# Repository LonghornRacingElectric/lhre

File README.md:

# LHRe

Documentation: https://docs.lhre.org

Longhorn Racing Electric's monorepo: firmware for every ECU on the car, the
hardware abstraction layer it's built on, and the tooling to build, test, and
flash it all with Bazel.

<div class="grid cards" markdown>

-   :material-swap-horizontal:{ .lg .middle } **CAN Matrix & Signals**

    ---

    Full CAN ID allocation, message timings, signal bit layouts, and telemetry bindings generated from spec.

    [:octicons-arrow-right-24: Open CAN Matrix](docs/can-matrix.md){ .md-button .md-button--primary }

-   :material-chip:{ .lg .middle } **Boards & Firmware**

    ---

    Per-ECU firmware layout, the VCU reference board, pinouts, and the new-board scaffolder.

    [:octicons-arrow-right-24: Explore Boards](boards/README.md){ .md-button }

-   :material-layers-outline:{ .lg .middle } **LHAL & Drivers**

    ---

    Platform-independent hardware abstraction layer enabling 100% host-testable embedded code.

    [:octicons-arrow-right-24: Read LHAL Guide](drivers/lhal/README.md){ .md-button }

-   :material-bug-outline:{ .lg .middle } **Hardware Debugging**

    ---

    Zero-setup VS Code debugging with ST-Link, hermetic gdb, OpenOCD, and SVD peripheral viewer.

    [:octicons-arrow-right-24: Debugging Guide](tools/debug/README.md){ .md-button }

</div>

## Layout

| Directory  | What lives there |
| ---------- | ---------------- |
| [`drivers/`](drivers/README.md) | Hardware. [LHAL](drivers/lhal/README.md) (our platform-independent HAL) and [vendor HAL packages](drivers/stm32/README.md). |
| [`lib/`](lib/README.md)     | Platform-agnostic C++ that builds on host **and** target (ring buffers, CRC, CAN pack/unpack, …), with colocated tests. |
| [`apps/`](apps/README.md)    | Host-side software: telemetry, dashboards, gateways. |
| [`boards/`](boards/README.md)  | Per-ECU firmware projects ([`boards/VCU`](boards/VCU/README.md) is the reference layout). |
| [`tools/`](tools/README.md)   | Build and dev tooling: [`firmware_project`](tools/firmware/README.md), flashing, [VS Code debugging](tools/debug/README.md), formatting. |
| [`autonomy/`](https://github.com/LonghornRacingElectric/lhre/tree/main/autonomy) | The driverless stack: ROS 2 Jazzy + Gazebo, built with colcon rather than Bazel ([ADR-009](docs/architecture/009-autonomy-outside-bazel.md)). |
| [`simulation/`](simulation/README.md) | Vehicle dynamics studies on [BobSim](https://github.com/BobDyn/BobSim), run with Make and Docker rather than Bazel ([ADR-012](docs/architecture/012-simulation-outside-bazel.md)). |
| [`vehicle/`](vehicle/README.md) | The current car's parameters (`vehicle.yml`, tire models). One source for simulation and any Bazel target. |

There are no per-year directories: `main` is always the current car, and past
seasons live in tags and maintenance branches (see
[CONTRIBUTING.md](CONTRIBUTING.md#season-policy)).

The decisions that shape the repo — monorepo, Bazel, LHAL, docs conventions
— are recorded as ADRs in [docs/architecture](docs/architecture/README.md).
The build system gets its own long-form record — why Bazel, and the whys
behind its forks, pins, and patches — in
[docs/build-system.md](docs/build-system.md).

## Prerequisites

- [Bazelisk](https://github.com/bazelbuild/bazelisk) (installs the pinned
  Bazel from `.bazelversion` automatically)
- Git

That's it — compilers (ARM GCC for firmware, LLVM for host code) are hermetic
and downloaded by Bazel. No Xcode, MSVC, or system GCC needed for C++, and
no MSYS2 or Git Bash on Windows: builds there are shell-free
([ADR-018](docs/architecture/018-windows-shell-free.md)).
STM32CubeMX is only needed when changing a board's peripheral configuration.

On Windows, builds run locally instead of on remote executors; for full remote
execution use WSL2 (see the comments in [.bazelrc](https://github.com/LonghornRacingElectric/lhre/blob/main/.bazelrc)).
Windows also needs the `startup --output_user_root=C:/_bzl` line uncommented
in `.bazelrc.user` (copied from
[.bazelrc.user.example](https://github.com/LonghornRacingElectric/lhre/blob/main/.bazelrc.user.example)) —
without it, Python codegen tools blow Windows' 260-char path limit and die
with an `ImportError` in the protobuf runtime.

## The commands

Everything goes through Bazel, and the surface is small enough to memorize.
Shown for the VCU; swap `VCU`/`vcu` for any board — the targets are uniform
because [`firmware_project`](tools/firmware/README.md) generates them.

| To…                        | Run |
| -------------------------- | --- |
| Build one board's firmware | `bazel build //boards/VCU:vcu` |
| Build + test everything    | `bazel test //...` |
| Test host C++ under UBSan  | `bazel test --config=ubsan //boards/... //drivers/...` ([more](tools/ubsan/README.md)) |
| Run a board's simulator    | `bazel run --config=local //boards/VCU:vcu_sim` |
| Flash over ST-Link         | `bazel run //boards/VCU:openocd` |
| Flash over USB (DFU)       | `bazel run //boards/VCU:dfu` |
| Format all C/C++           | `bazel run //tools/format` |
| Fix IDE red squiggles      | `bazel run //:refresh_ide` |

`bazel test //...` runs on the BuildBuddy Linux executors by default (see
below); add `--config=local` to any command to stay entirely on your
machine. Green `bazel test //...` on a fresh clone means you're set up —
there is nothing else to install.

When the convention doesn't cover you — a file the build won't pick up, a
new dependency, vendoring a library, a test target that isn't found — see
the [cookbook](docs/cookbook.md).

Debug on hardware: open the repo in VS Code, install the recommended
Cortex-Debug extension, plug in the ST-Link, and hit F5 — breakpoints,
FreeRTOS thread views, and peripheral registers, with nothing else to
install on any OS (see
[CONTRIBUTING.md](CONTRIBUTING.md#debugging-on-hardware-vs-code)).

## Remote build setup (BuildBuddy)

Builds stream to and cache on [lhre.buildbuddy.io](https://lhre.buildbuddy.io).
To authenticate, copy [.bazelrc.user.example](https://github.com/LonghornRacingElectric/lhre/blob/main/.bazelrc.user.example) to
`.bazelrc.user` (gitignored) and paste your API key from BuildBuddy →
Settings → API keys — ask a software lead for an invite to the org.

No key, or no internet? `--config=local` builds entirely on your machine.

## License

MIT, see [LICENSE](https://github.com/LonghornRacingElectric/lhre/blob/main/LICENSE).

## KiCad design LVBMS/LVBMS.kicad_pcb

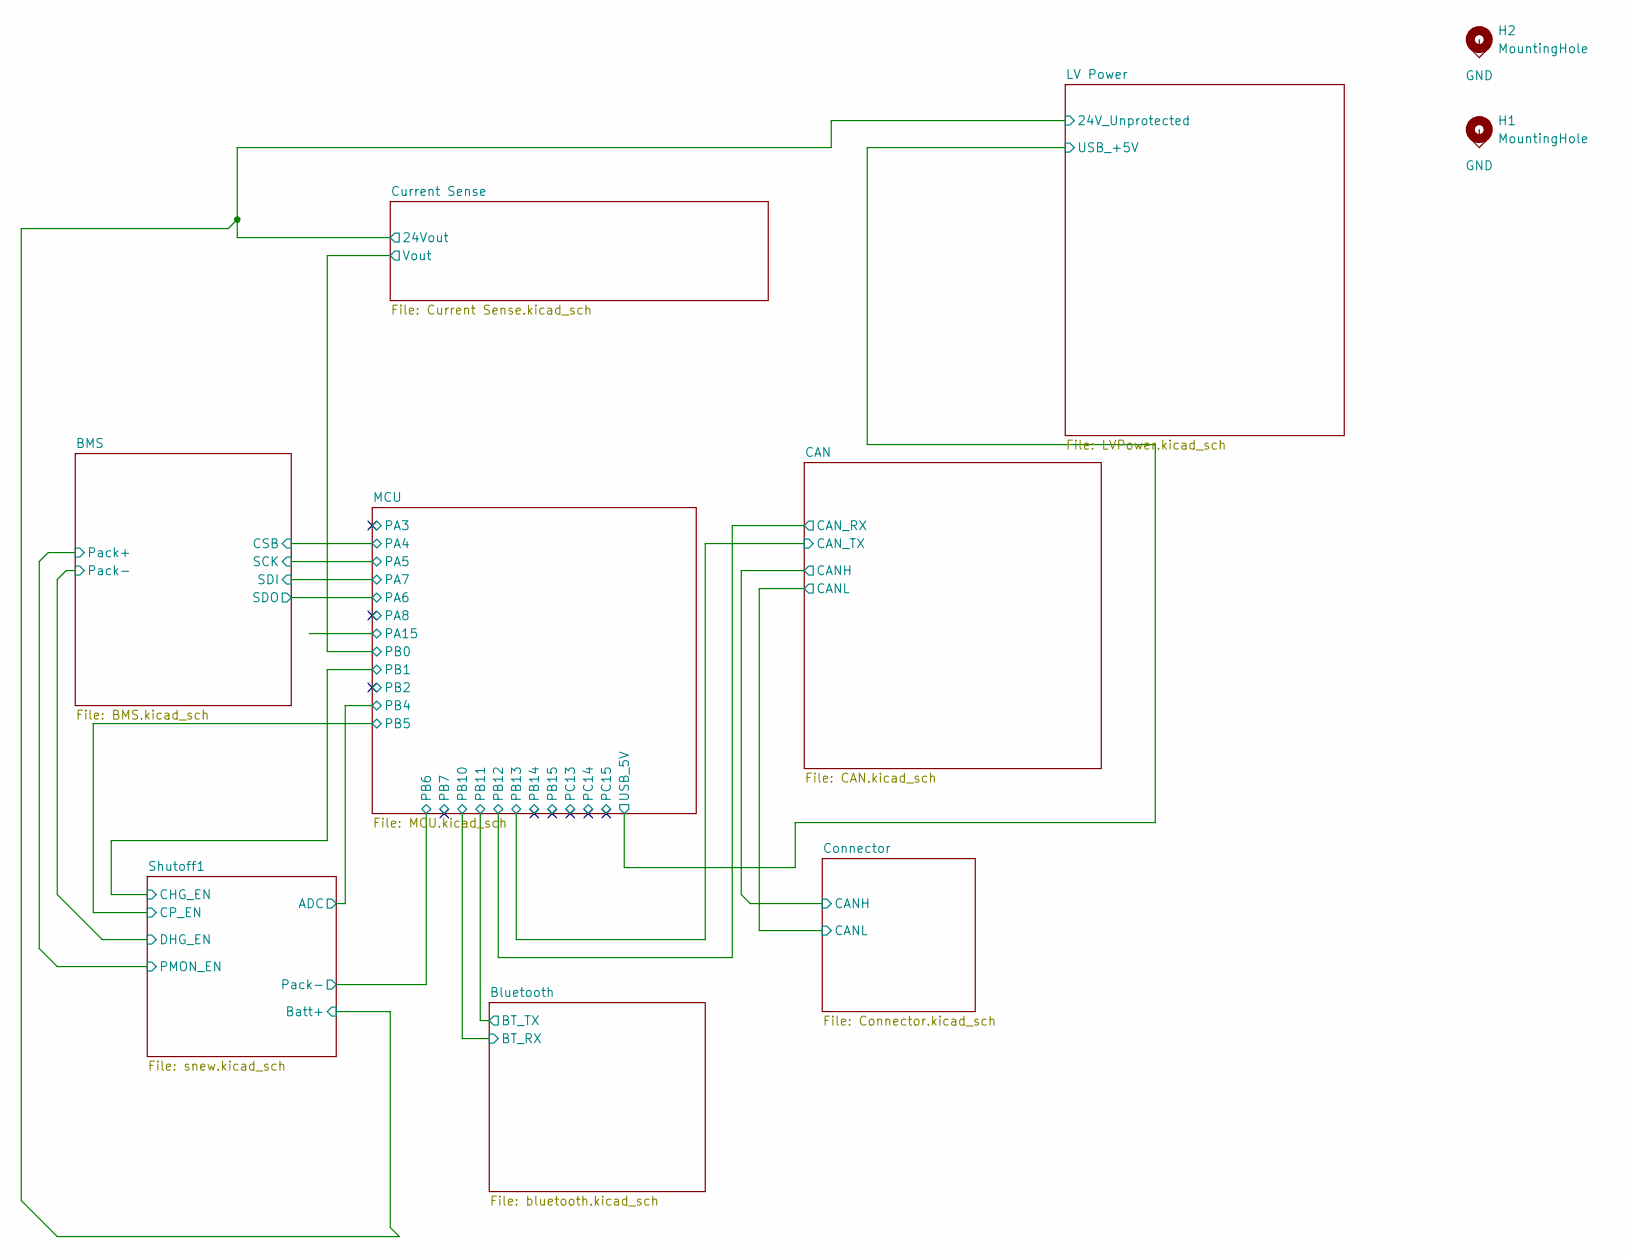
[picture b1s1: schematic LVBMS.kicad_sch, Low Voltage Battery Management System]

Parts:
H1, H2: MountingHole; MountingHole_3.2mm_M3

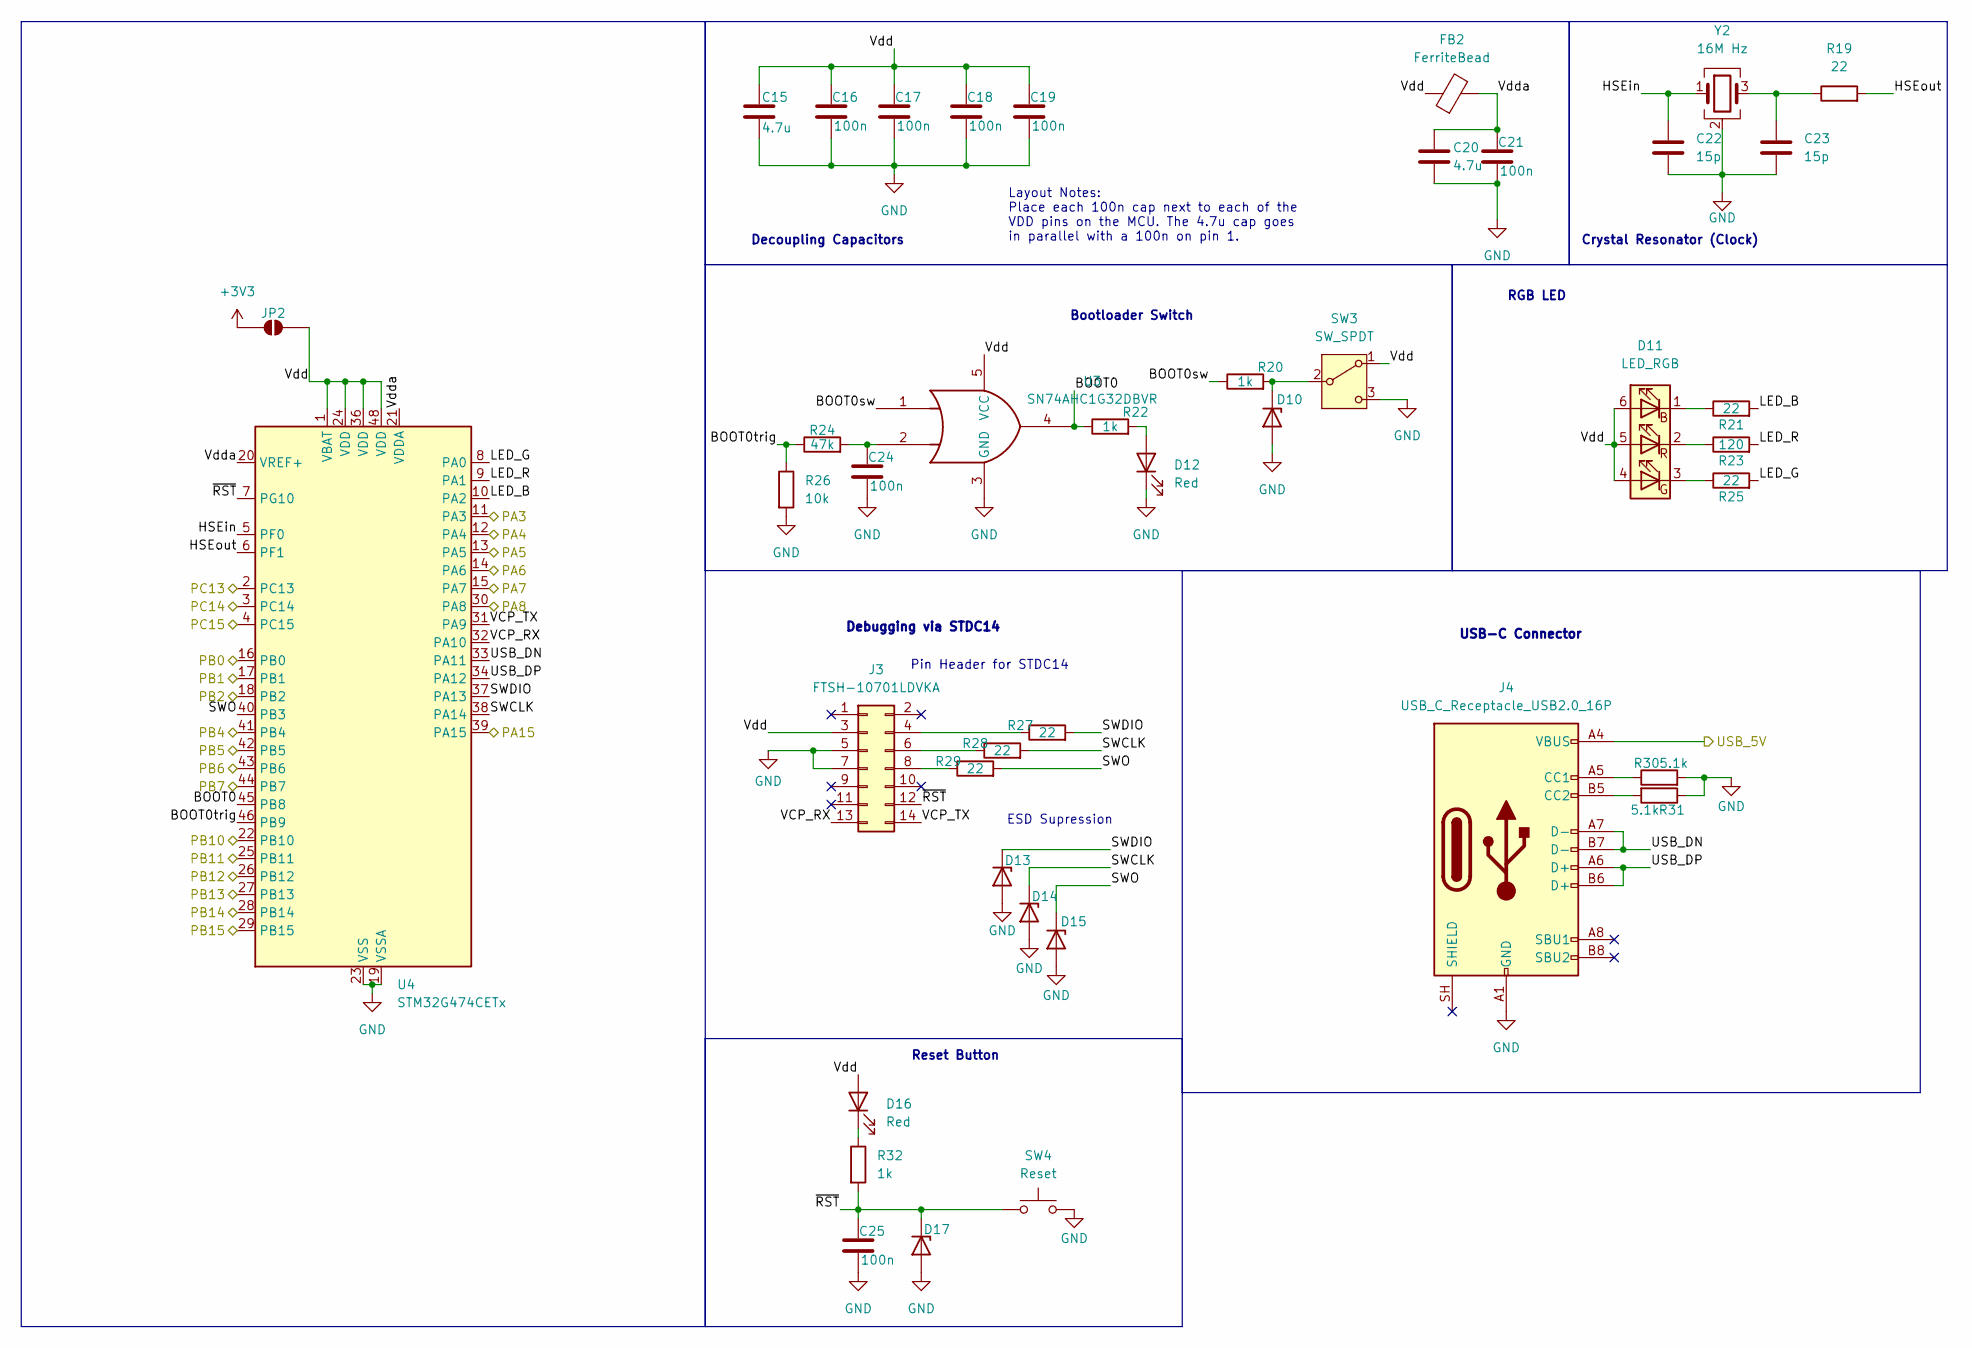
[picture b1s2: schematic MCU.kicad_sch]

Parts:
C15, C20: 4.7u; C_1206_3216Metric; Mouser # 187-CL31A475KBHNNNE; JLCPCB # C513768
C16, C17, C18, C19, C21, C24, C25: 100n; C_0603_1608Metric; Mouser # 603-CC603KRX7R9BB104; JLCPCB # C14663
C22, C23: 15p; C_0603_1608Metric; Mouser # 187-CL10C150JB8NNNC; JLCPCB # C1644
D10, D13, D14, D15, D17: ESD5Z3.3T1G; D_SOD-523; Mouser # 863-ESD5Z3.3T1G; JLCPCB # C61148
D11: LED_RGB; LED_RGB_5050-6; Mouser # 710-150505M173300; JLCPCB # C3975087
D12, D16: Red; D_0603_1608Metric; Mouser # 755-CSL1901UW1; JLCPCB # C2286
FB2: FerriteBead; R_0603_1608Metric; Mouser # 81-BLM18KN601EH1D; JLCPCB # C1002
J3: FTSH-10701LDVKA; FTSH-107-XX-YYY-DV-K-A; Mouser # 200-FTSH10701LDVKA; JLCPCB # C5563894
J4: USB_C_Receptacle_USB2.0_16P; USB-C_2.0_Receptacle; Mouser # 640-USB4105-GF-A; JLCPCB # C2982555
JP2: SolderJumper_2_Open; SolderJumper-2_P1.3mm_Open_RoundedPad1.0x1.5mm; Mouser # N/A
R19, R21, R25, R27, R28, R29: 22; R_0603_1608Metric; Mouser # 303-0603WAF220JT5E; JLCPCB # C23345
R20, R22, R32: 1k; R_0603_1608Metric; Mouser # 303-0603WAF1001T5E; JLCPCB # C21190
R23: 120; R_0603_1608Metric; Mouser # 303-0603WAF1200T5E; JLCPCB # C22787
R24: 47k; R_0603_1608Metric; Mouser # 303-0603WAF4702T5E; JLCPCB # C25819
R26: 10k; R_0603_1608Metric; Mouser # 303-0603WAF1002T5E; JLCPCB # C25804
R30, R31: 5.1k; R_0603_1608Metric; Mouser # 303-0603WAF5101T5E; JLCPCB # C23186
SW3: SW_SPDT; SW_SPDT_PCM12; Mouser # 611-PCM12SMTBR; JLCPCB # C319020
SW4: Reset; 19772231; Mouser # 506-1977223-1; JLCPCB # C381039
U3: SN74AHC1G32DBVR; SOT-23-5; Mouser # 595-SN74AHC1G32DBVR; JLCPCB # C7470
U4: STM32G474CETx; LQFP-48_7x7mm_P0.5mm; Mouser # 511-STM32G474CCT6; JLCPCB # C730124
Y2: 16M Hz; Crystal_SMD_3225-4Pin_3.2x2.5mm; Mouser # ECS-160-8-33B-CTN-TR; JLCPCB # C2875244

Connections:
+3V3: JP2.1 (A); also elsewhere on the board
/BMS/CSB: U4.12 (PA4); also elsewhere on the board
/BMS/SCK: U4.13 (PA5); also elsewhere on the board
/BMS/SDI: U4.15 (PA7); also elsewhere on the board
/BMS/SDO: U4.14 (PA6); also elsewhere on the board
/Bluetooth/BT_RX: U4.22 (PB10); also elsewhere on the board
/Bluetooth/BT_TX: U4.25 (PB11); also elsewhere on the board
/CAN/CAN_RX: U4.26 (PB12); also elsewhere on the board
/CAN/CAN_TX: U4.27 (PB13); also elsewhere on the board
/Current Sense/Vout: U4.16 (PB0); also elsewhere on the board
/LV Power/USB_+5V: J4.A4 (VBUS), J4.A9 (VBUS), J4.B4 (VBUS), J4.B9 (VBUS); also elsewhere on the board
/MCU/BOOT0: R22.1, U3.4, U4.45 (PB8)
/MCU/BOOT0sw: R20.1, U3.1
/MCU/BOOT0trig: R24.1, R26.1, U4.46 (PB9)
/MCU/HSEin: C22.1, U4.5 (PF0), Y2.1
/MCU/HSEout: R19.2, U4.6 (PF1)
/MCU/LED_B: R21.2, U4.10 (PA2)
/MCU/LED_G: R25.2, U4.8 (PA0)
/MCU/LED_R: R23.2, U4.9 (PA1)
/MCU/PA3: U4.11 (PA3)
/MCU/PA8: U4.30 (PA8); also elsewhere on the board
/MCU/PA15: U4.39 (PA15)
/MCU/PB1: U4.17 (PB1); also elsewhere on the board
/MCU/PB2: U4.18 (PB2); also elsewhere on the board
/MCU/PB4: U4.41 (PB4); also elsewhere on the board
/MCU/PB5: U4.42 (PB5); also elsewhere on the board
/MCU/PB7: U4.44 (PB7)
/MCU/PB14: U4.28 (PB14)
/MCU/PB15: U4.29 (PB15)
/MCU/PC13: U4.2 (PC13)
/MCU/PC14: U4.3 (PC14)
/MCU/PC15: U4.4 (PC15)
/MCU/SWCLK: D14.1 (K), R28.2, U4.38 (PA14)
/MCU/SWDIO: D13.1 (K), R27.2, U4.37 (PA13)
/MCU/SWO: D15.1 (K), R29.2, U4.40 (PB3)
/MCU/USB_DN: J4.A7 (D-), J4.B7 (D-), U4.33 (PA11)
/MCU/USB_DP: J4.A6 (D+), J4.B6 (D+), U4.34 (PA12)
/MCU/VCP_RX: J3.13, U4.32 (PA10)
/MCU/VCP_TX: J3.14, U4.31 (PA9)
/MCU/Vdd: C15.1, C16.1, C17.1, C18.1, C19.1, D11.4 (BK), D11.5 (GK), D11.6 (RK), D16.2 (A), FB2.1, J3.3, JP2.2 (B), SW3.1 (A), U3.5 (VCC), U4.1 (VBAT), U4.24 (VDD), U4.36 (VDD), U4.48 (VDD)
/MCU/Vdda: C20.1, C21.1, FB2.2, U4.20 (VREF+), U4.21 (VDDA)
/MCU/~RST: C25.1, D17.1 (K), J3.12, R32.2, SW4.1, U4.7 (PG10)
GND: C15.2, C16.2, C17.2, C18.2, C19.2, C20.2, C21.2, C22.2, C23.2, C24.2, C25.2, D10.2 (A), D12.1 (K), D13.2 (A), D14.2 (A), D15.2 (A), D17.2 (A), J3.5, J3.7, J4.A1 (GND), J4.A12 (GND), J4.B1 (GND), J4.B12 (GND), R26.2, R30.2, R31.1, SW3.3 (C), SW4.2, U3.3 (GND), U4.19 (VSSA), U4.23 (VSS), U4.35 (VSS), U4.43 (PB6), U4.47 (VSS), Y2.2 (G), Y2.4 (G); also elsewhere on the board
unnamed: C23.1, R19.1, Y2.3
unnamed: C24.1, R24.2, U3.2
unnamed: D10.1 (K), R20.2, SW3.2 (B)
unnamed: D11.3 (BA), R25.1
unnamed: D11.2 (GA), R23.1
unnamed: D11.1 (RA), R21.1
unnamed: D12.2 (A), R22.2
unnamed: D16.1 (K), R32.1
unnamed: J3.4, R27.1
unnamed: J3.6, R28.1
unnamed: J3.8, R29.1
unnamed: J4.A5 (CC1), R30.1
unnamed: J4.B5 (CC2), R31.2

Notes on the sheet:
Crystal Resonator (Clock)
ESD Supression
USB-C Connector
Pin Header for STDC14
Bootloader Switch
Debugging via STDC14
Reset Button
RGB LED
Layout Notes: Place each 100n cap next to each of the VDD pins on the MCU. The 4.7u cap goes in parallel with a 100n on pin 1.
Decoupling Capacitors

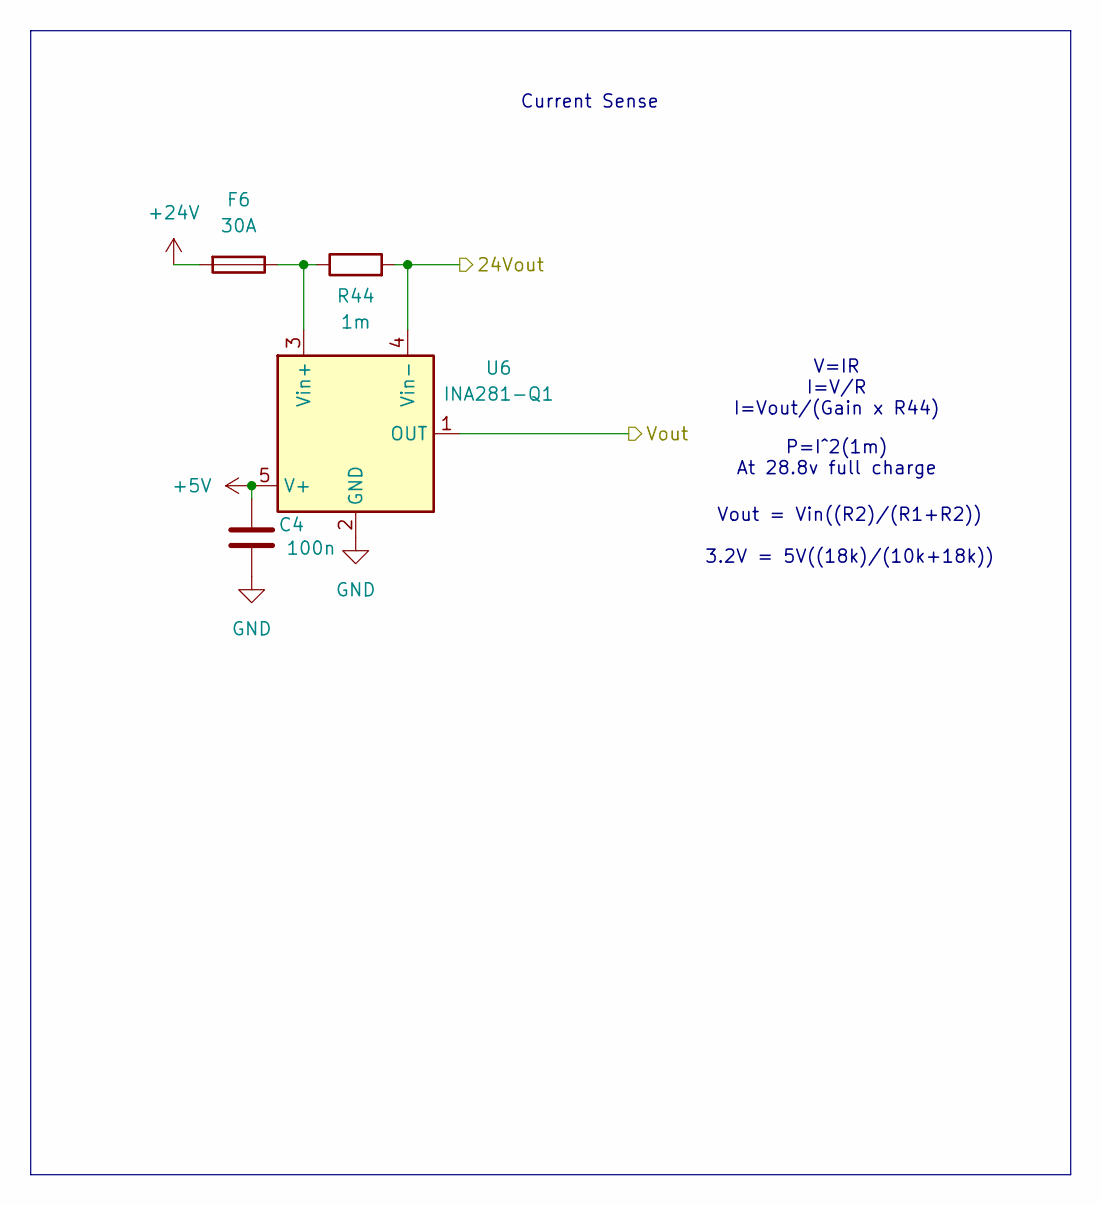
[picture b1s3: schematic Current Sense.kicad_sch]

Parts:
C4: 100n; SOIC-8_3.9x4.9mm_P1.27mm
F6: 30A; Fuseholder_Blade_Mini_Keystone_3568
R44: 1m; R_2010_5025Metric_Pad1.40x2.65mm_HandSolder; Mouser # 652-CRF2010FZR001ELF
U6: INA281-Q1; SOT-23-5; Mouser # 595-INA281A3QDBVRQ1

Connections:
+5V: C4.1, U6.5 (V+); also elsewhere on the board
+24V: F6.2; also elsewhere on the board
/Current Sense/24Vout: R44.2, U6.4 (Vin-); also elsewhere on the board
/Current Sense/Vout: U6.1 (OUT); also elsewhere on the board
GND: C4.2, U6.2 (GND); also elsewhere on the board
unnamed: F6.1, R44.1, U6.3 (Vin+)

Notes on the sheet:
P=I^2(1m) At 28.8v full charge
Current Sense
Vout = Vin((R2)/(R1+R2)) 3.2V = 5V((18k)/(10k+18k))
V=IR I=V/R I=Vout/(Gain x R44)

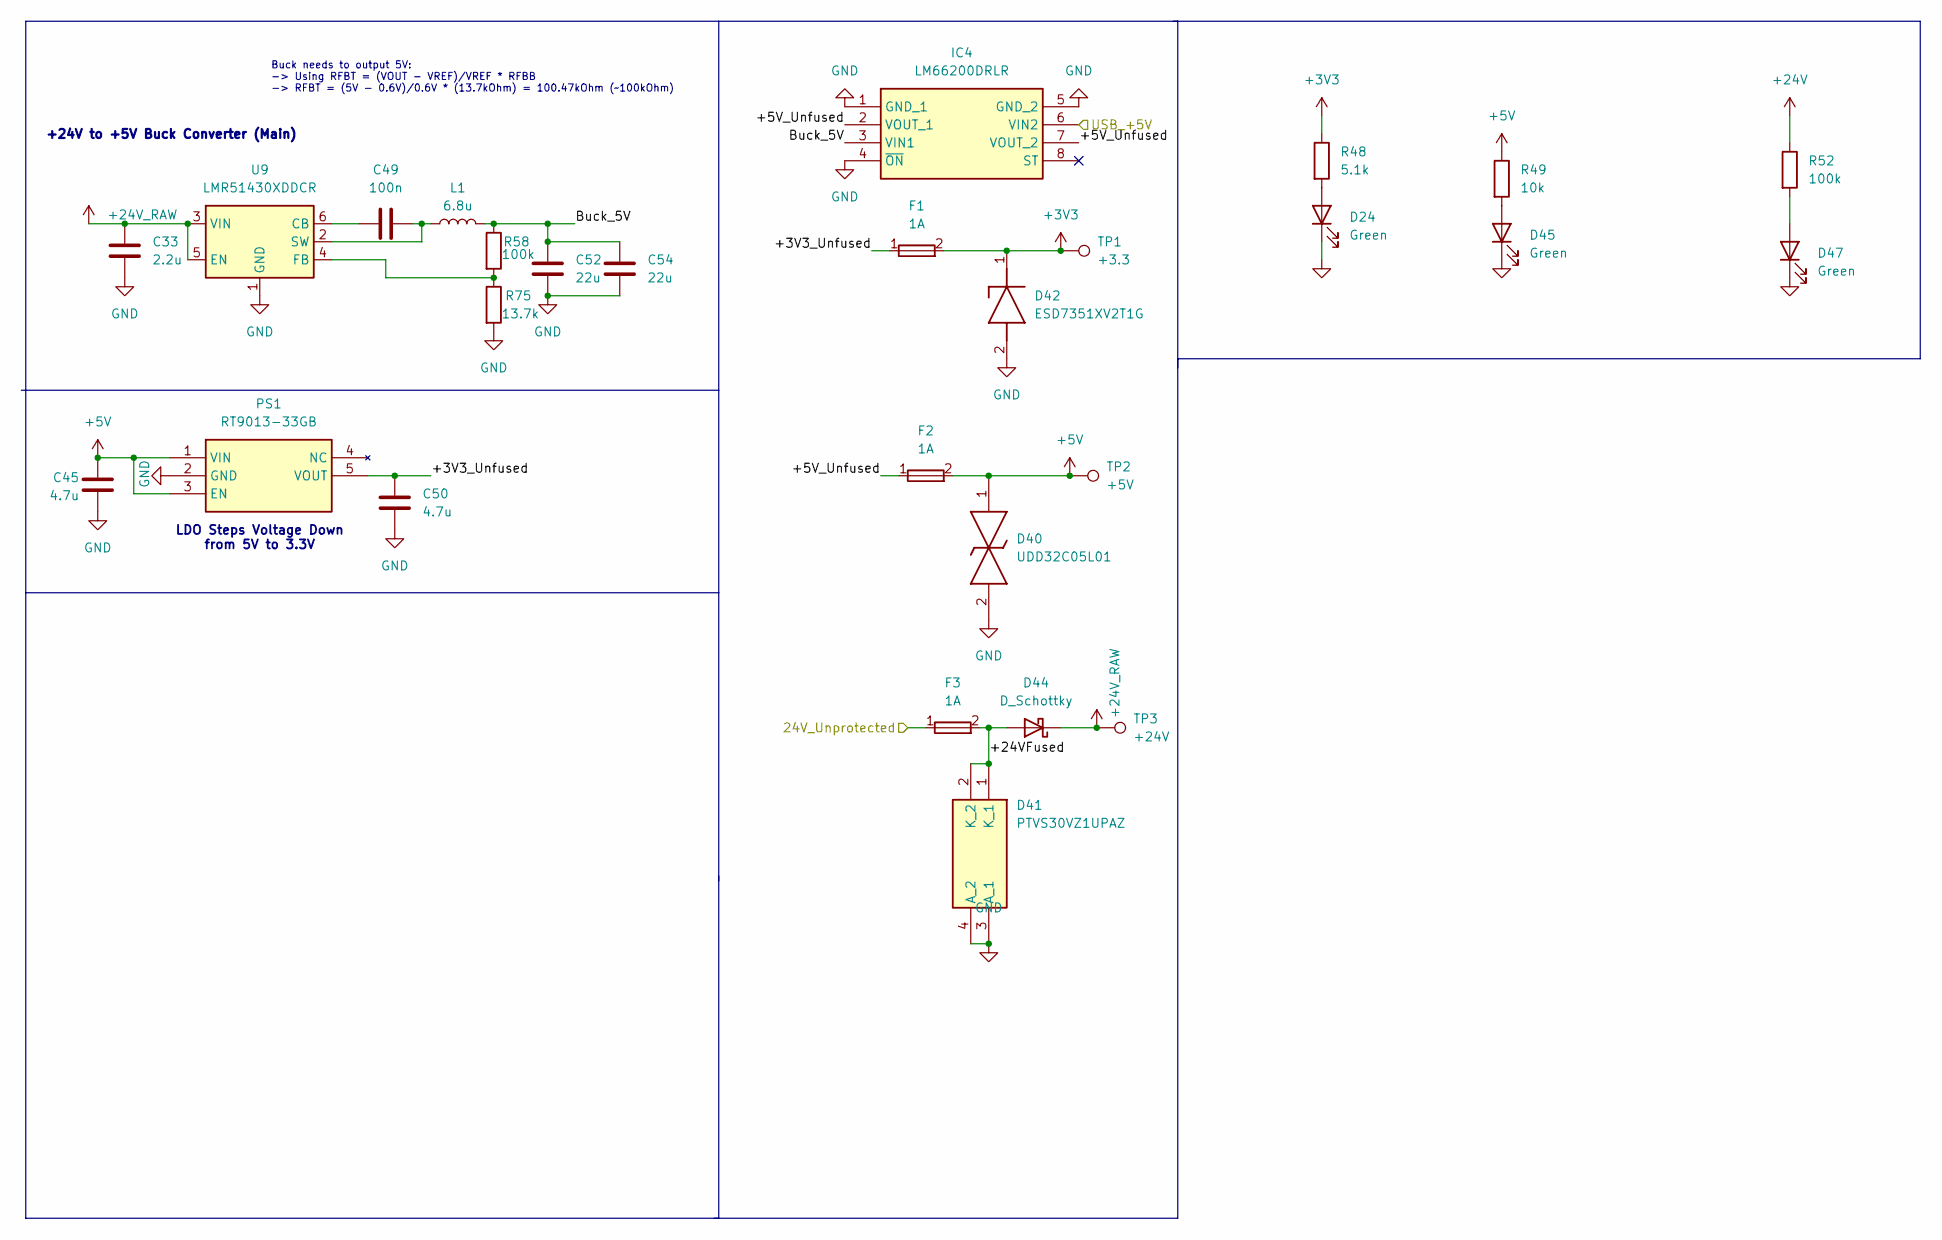
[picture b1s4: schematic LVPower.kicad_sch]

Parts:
C33: 2.2u; C_0603_1608Metric; Mouser # 81-GRM188R61H225KE1D; JLCPCB # C162273
C45, C50: 4.7u; C_1206_3216Metric; Mouser # 187-CL31A475KBHNNNE; JLCPCB # C513768
C49: 100n; C_0603_1608Metric; Mouser # 603-CC603KRX7R9BB104; JLCPCB # C14663
C52, C54: 22u; C_0603_1608Metric; Mouser # 81-GRM188R61A226ME5D; JLCPCB # C84419
D24, D45, D47: Green; D_0603_1608Metric; Mouser # 604-APT1608LZGCK; JLCPCB # C5246833
D40: UDD32C05L01; D_SOD-323; Mouser # 603-UDD32C05L01; JLCPCB # C78440
D41: PTVS30VZ1UPAZ; Mouser # 771-PTVS30VZ1UPAZ; JLCPCB # C22421832
D42: ESD7351XV2T1G; SODFL1608X70N; Mouser # 863-ESD7351XV2T1G; JLCPCB # C890625
D44: D_Schottky; D_PowerDI-123; Mouser # 621-DFLS160-F; JLCPCB # C177023
F1, F2, F3: 1A; Fuse_0603_1608Metric; Mouser # 576-0467001.NRHF; JLCPCB # C136329
IC4: LM66200DRLR; SOTFL50P160X60-8N; Mouser # 595-LM66200DRLR; JLCPCB # C3235556
L1: 6.8u; L_Changjiang_FTC404020S; Mouser # 710-74405042068; JLCPCB # C843301
PS1: RT9013-33GB; SOT94P279X130-5N; Mouser # 835-RT9013-33GB; JLCPCB # C47773
R48: 5.1k; R_0603_1608Metric; Mouser # 303-0603WAF5101T5E; JLCPCB # C23186
R49: 10k; R_0603_1608Metric; Mouser # 303-0603WAF1002T5E; JLCPCB # C25804
R52, R58: 100k; R_0603_1608Metric; Mouser # 603-RC0603FR-07100KL; JLCPCB # C14675
R75: 13.7k; R_0603_1608Metric; Mouser # 303-0603WAF1372T5E; JLCPCB # C22793
TP1: +3.3; TestPoint_Keystone_5010-5014_Multipurpose; Mouser # N/A
TP2: +5V; TestPoint_Keystone_5010-5014_Multipurpose; Mouser # N/A
TP3: +24V; TestPoint_Keystone_5010-5014_Multipurpose; Mouser # N/A
U9: LMR51430XDDCR; SOT-23-6; Mouser # 595-LMR51430XDDCR; JLCPCB # C5185863

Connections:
+3V3: D42.1 (K), F1.2, R48.1, TP1.1 (1_1); also elsewhere on the board
+5V: C45.1, D40.1, F2.2, PS1.1 (VIN), PS1.3 (EN), R49.1, TP2.1 (1_1); also elsewhere on the board
+24V: R52.1; also elsewhere on the board
+24V_RAW: C33.1, D44.1 (K), TP3.1 (1_1), U9.3 (VIN), U9.5 (EN)
/Current Sense/24Vout: F3.1; also elsewhere on the board
/LV Power/+3V3_Unfused: C50.1, F1.1, PS1.5 (VOUT)
/LV Power/+5V_Unfused: F2.1, IC4.2 (VOUT_1), IC4.7 (VOUT_2)
/LV Power/+24VFused: D41.1 (K_1), D41.2 (K_2), D44.2 (A), F3.2
/LV Power/Buck_5V: C52.1, C54.1, IC4.3 (VIN1), L1.2, R58.1
/LV Power/USB_+5V: IC4.6 (VIN2); also elsewhere on the board
GND: C33.2, C45.2, C50.2, C52.2, C54.2, D24.1 (K), D40.2, D41.3 (A_1), D41.4 (A_2), D42.2 (A), D45.1 (K), D47.1 (K), IC4.1 (GND_1), IC4.4 (~ON), IC4.5 (GND_2), PS1.2 (GND), R75.2, U9.1 (GND); also elsewhere on the board
unnamed: D24.2 (A), R48.2
unnamed: D45.2 (A), R49.2
unnamed: D47.2 (A), R52.2
unnamed: C49.1, U9.6 (CB)
unnamed: R58.2, R75.1, U9.4 (FB)
unnamed: C49.2, L1.1, U9.2 (SW)

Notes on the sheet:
+24V to +5V Buck Converter (Main)
Buck needs to output 5V: -> Using RFBT = (VOUT - VREF)/VREF * RFBB -> RFBT = (5V - 0.6V)/0.6V * (13.7kOhm) = 100.47kOhm (~100kOhm)
LDO Steps Voltage Down from 5V to 3.3V

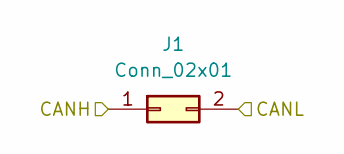
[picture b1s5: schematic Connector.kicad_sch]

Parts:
J1: Conn_02x01; Molex_Micro-Fit_3.0_43650-0221_1x02_P3.00mm_Vertical

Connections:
/CAN/CANH: J1.1; also elsewhere on the board
/CAN/CANL: J1.2; also elsewhere on the board

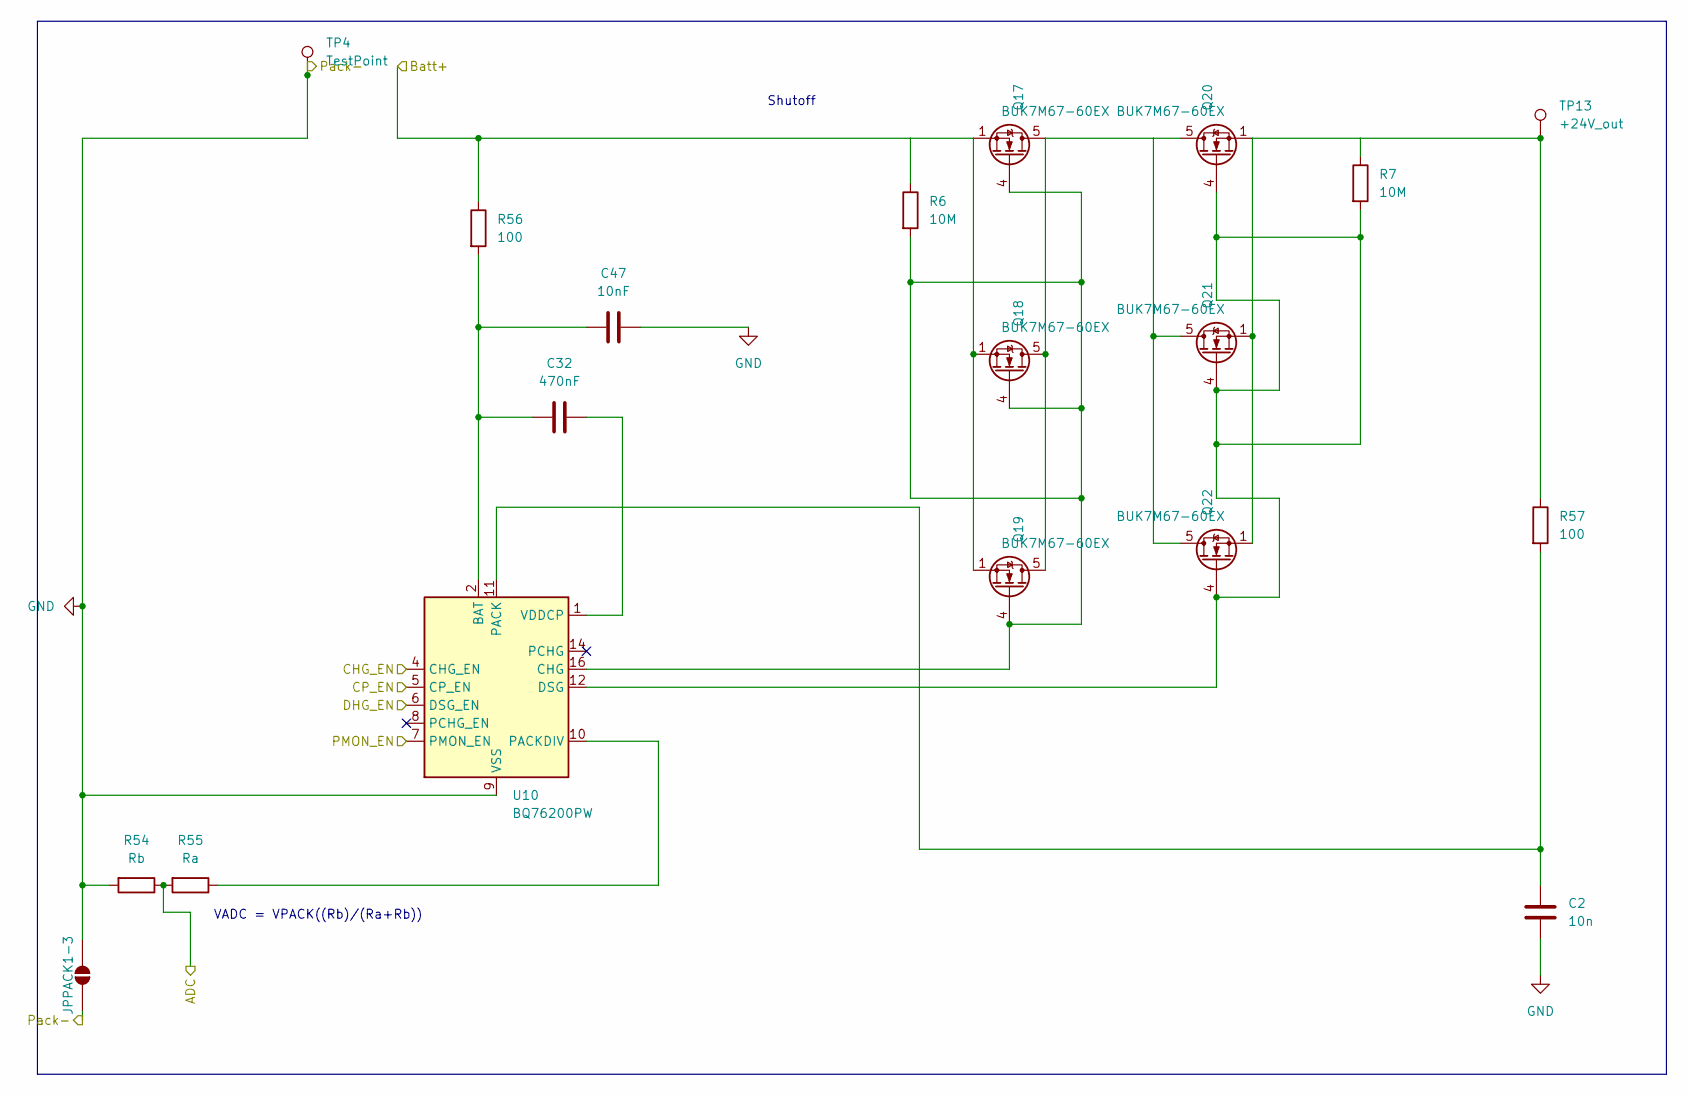
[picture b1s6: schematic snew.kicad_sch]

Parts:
C2: 10n; C_0603_1608Metric_Pad1.08x0.95mm_HandSolder
C32: 470nF; C_2220_5750Metric_Pad1.97x5.40mm_HandSolder
C47: 10nF; LED_Kingbright_APFA3010_3x1.5mm_Horizontal
JPPACK1-3: SolderJumper_2_Open; SolderJumper-2_P1.3mm_Open_RoundedPad1.0x1.5mm; Mouser # N/A
Q17, Q18, Q19, Q20, Q21, Q22: BUK7M67-60EX; LFPAK33
R6, R7: 10M; R_1210_3225Metric_Pad1.30x2.65mm_HandSolder
R54: Rb; R_0603_1608Metric
R55: Ra; R_0603_1608Metric
R56, R57: 100; R_0603_1608Metric
TP4: TestPoint; TestPoint_Keystone_5010-5014_Multipurpose
TP13: +24V_out; TestPoint_Keystone_5010-5014_Multipurpose
U10: BQ76200PW; TSSOP-16_4.4x5mm_P0.65mm

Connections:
/Current Sense/24Vout: Q17.1 (S), Q17.2 (S), Q17.3 (S), Q18.1 (S), Q18.2 (S), Q18.3 (S), Q19.1 (S), Q19.2 (S), Q19.3 (S), R6.1, R56.1; also elsewhere on the board
/MCU/PA8: U10.7 (PMON_EN); also elsewhere on the board
/MCU/PB1: U10.4 (CHG_EN); also elsewhere on the board
/MCU/PB2: U10.6 (DSG_EN); also elsewhere on the board
/MCU/PB4: R54.1, R55.2; also elsewhere on the board
/MCU/PB5: U10.5 (CP_EN); also elsewhere on the board
GND: C2.2, C47.1, JPPACK1-3.1 (A), JPPACK1-3.2 (B), R54.2, TP4.1 (1_1), U10.9 (VSS); also elsewhere on the board
unnamed: Q17.5 (D), Q18.5 (D), Q19.5 (D), Q20.5 (D), Q21.5 (D), Q22.5 (D)
unnamed: Q17.4 (G), Q18.4 (G), Q19.4 (G), R6.2, U10.16 (CHG)
unnamed: Q20.4 (G), Q21.4 (G), Q22.4 (G), R7.2, U10.12 (DSG)
unnamed: Q20.1 (S), Q20.2 (S), Q20.3 (S), Q21.1 (S), Q21.2 (S), Q21.3 (S), Q22.1 (S), Q22.2 (S), Q22.3 (S), R7.1, R57.1, TP13.1 (1_1)
unnamed: C32.2, C47.2, R56.2, U10.2 (BAT)
unnamed: C2.1, R57.2, U10.11 (PACK)
unnamed: R55.1, U10.10 (PACKDIV)
unnamed: C32.1, U10.1 (VDDCP)

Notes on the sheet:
VADC = VPACK((Rb)/(Ra+Rb))
Shutoff

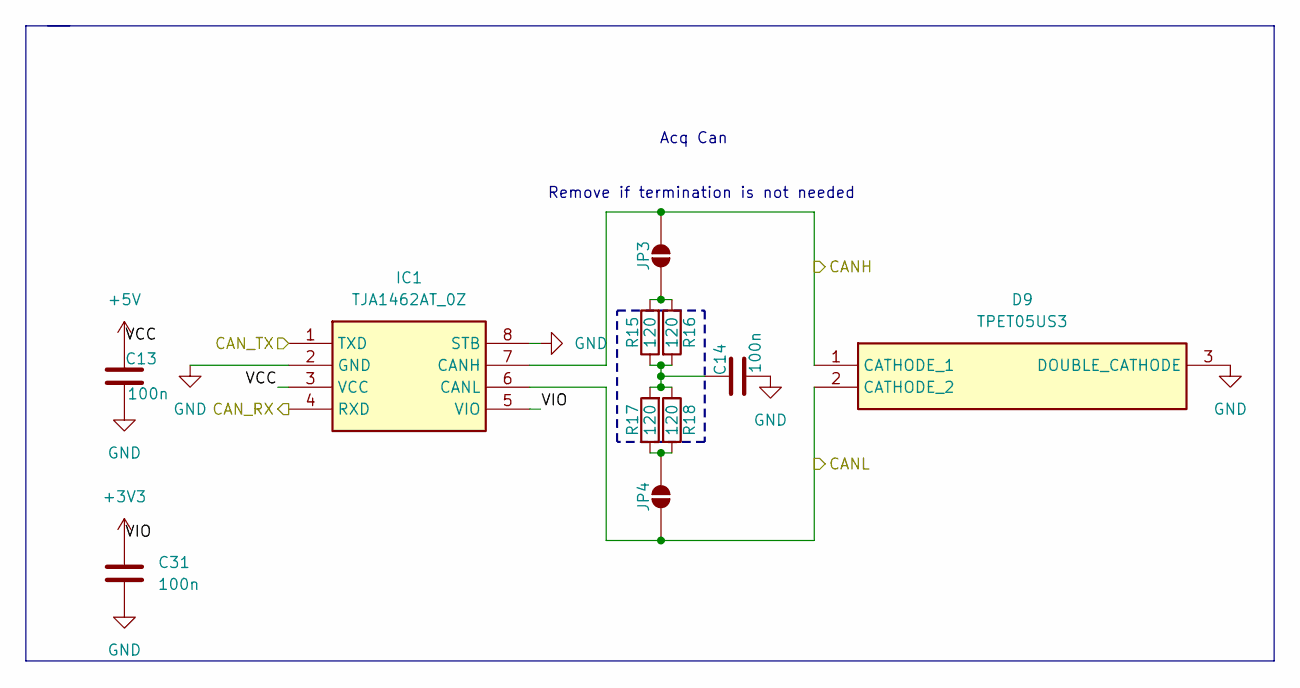
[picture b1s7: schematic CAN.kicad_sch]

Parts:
C13, C14, C31: 100n; C_0603_1608Metric; Mouser # 603-CC603KRX7R9BB104; JLCPCB # C14663
D9: TPET05US3; SOT-23; Mouser # 771-PESD3V3L2BT-T/R; JLCPCB # C55440
IC1: TJA1462AT_0Z; SOIC127P600X175-8N; Mouser # 771-TJA1462AT/0Z; JLCPCB # C3234095
JP3, JP4: SolderJumper_2_Open; SolderJumper-2_P1.3mm_Open_RoundedPad1.0x1.5mm; Mouser # N/A
R15, R16, R17, R18: 120; R_0603_1608Metric; Mouser # 303-0603WAF1200T5E; JLCPCB # C22787

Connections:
+3V3: C31.1, IC1.5 (VIO); also elsewhere on the board
+5V: C13.1, IC1.3 (VCC); also elsewhere on the board
/CAN/CANH: D9.1 (CATHODE_1), IC1.7 (CANH), JP3.2 (B); also elsewhere on the board
/CAN/CANL: D9.2 (CATHODE_2), IC1.6 (CANL), JP4.1 (A); also elsewhere on the board
/CAN/CAN_RX: IC1.4 (RXD); also elsewhere on the board
/CAN/CAN_TX: IC1.1 (TXD); also elsewhere on the board
GND: C13.2, C14.2, C31.2, D9.3 (DOUBLE_CATHODE), IC1.2 (GND), IC1.8 (STB); also elsewhere on the board
unnamed: C14.1, R15.1, R16.2, R17.2, R18.1
unnamed: JP3.1 (A), R15.2, R16.1
unnamed: JP4.2 (B), R17.1, R18.2

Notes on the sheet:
Remove if termination is not needed
Acq Can

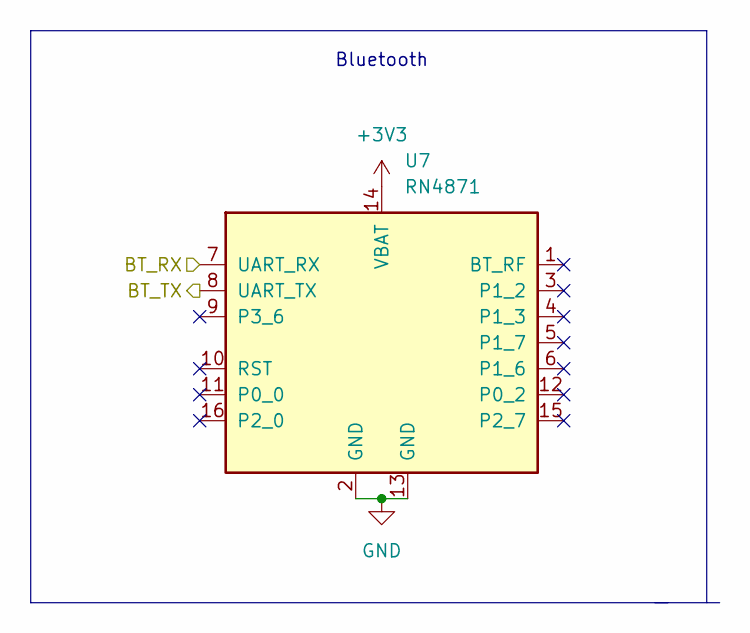
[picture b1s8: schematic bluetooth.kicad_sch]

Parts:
U7: RN4871; Microchip_RN4871; Mouser # 579-RN4871IRM130; JLCPCB # C633942

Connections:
+3V3: U7.14 (VBAT); also elsewhere on the board
/Bluetooth/BT_RX: U7.7 (UART_RX); also elsewhere on the board
/Bluetooth/BT_TX: U7.8 (UART_TX); also elsewhere on the board
GND: U7.2 (GND), U7.13 (GND); also elsewhere on the board

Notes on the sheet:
Bluetooth
